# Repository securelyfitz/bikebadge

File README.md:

# 503 party bike badge - 2015
http://503.party/
hardware and software files for attiny-based bicycle badge with rotating flashy reverse-mount LED wheels

## Hardware Description
This project is designed as the badge for donors to the 503 party fund in 2015. The circuit is inteded to use the minimum number of components to get a rotating wheel effect with the LEDs while having a completely clean PCB top side.

## Hardware Theory
Since the number of GPIOs are limited in a tiny chip, some fancy schematic-ing was done.
The bike handlebars (brakes slow down) and pedals (go faster) are two metal areas used as capacitive sensors. This takes up 3 pins - 1 to drive all of them, plus 1 for each sensor.
That leaves 2 pins to control 16 LEDs (14 in final revision for aesthetic reasons) that have to flash in a specific progression:
* the two wheels are identical, so really we need to drive 8 LED positions
* the wheels have two 'pulses' going around them, 180 degrees out of phase, so opposite LEDs are always identical. 4 LED positions
* If LEDs are identical 180 degrees out of phase, then they're opposite 90 degrees out of phase. That means half the LEDs are inversions of the other half. 2 LEDs positons.

If we wire 1 led between VCC and a GPIO, and a second one between a GPIO and GND, then one will be on when GPIO is 1, and the other will be on when GPIO is 0
If we do PWM, then (duty cycle B) = (1 - duty cycle A)
This makes very simple code possible

## Bill of Materials:
* 14x OSRAM reverse-gullwing LEDs (LYT776 YELLOW LED is what i used, 475-2801-1-ND)
* 14x 200 Ohm 1206 SMT Resistor (digikey 311-10MERCT-ND)
* 2x 10M Ohm 0805 Resistor (digikey RMCF0805JT10M0CT-ND)
* 1x ATTiny85 soic8 ()
* 1x 20mm through-hole CR2032 holder and battery

In quantity, BOM cost is about $2-$5 depending on if you can find the reverse-gullwing LEDs

##Building
All of the components are different sizes - if the pads line up it's in the right spot, just make sure pin 1 of the attiny aligns to the dot, and the 'noch' on the LEDS all point clockwise around the wheel.

##Software Description
This code is an Arduino sketch. I used the Sparkfun TinyAVR Programmer and follow the linked hookup guide to get it working: https://www.sparkfun.com/products/11801

The code for sensing the capacitive buttons is based on Paul Stoffregen's updated CapacitiveSensor libarry: https://github.com/PaulStoffregen/CapacitiveSensor
The LEDs are lit with PWM inside a loop. i is rotation point in radians of the wheel
```
for (float i=0;i<(3.1415*2);i+=(3.1415/revs)){
    analogWrite(pwm0,127*(cos(i)+1));
    analogWrite(pwm1,127*(sin(i)+1));
}
```

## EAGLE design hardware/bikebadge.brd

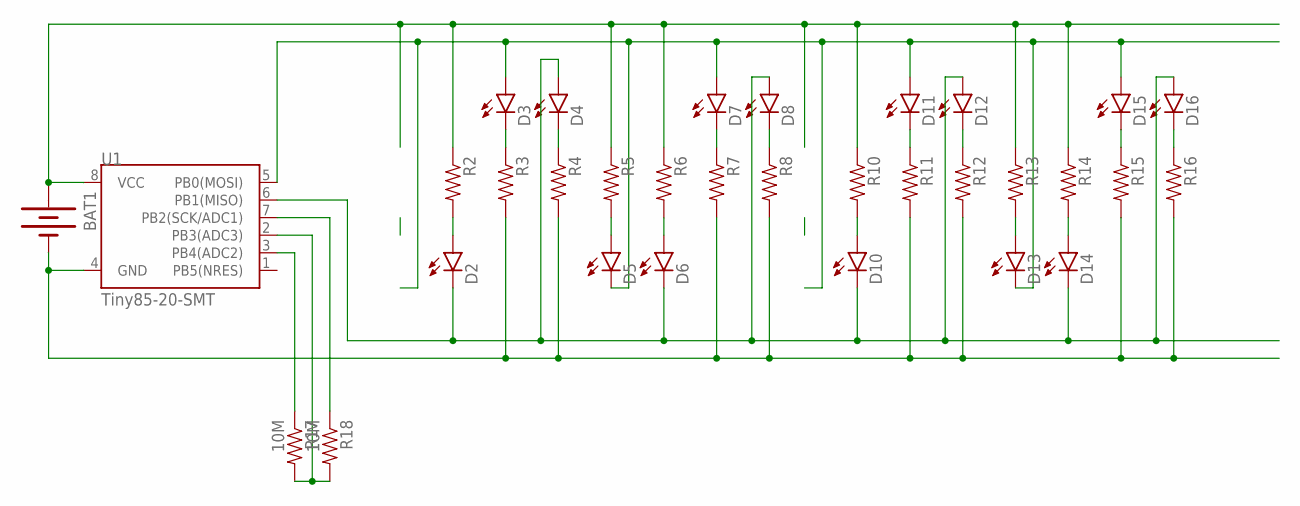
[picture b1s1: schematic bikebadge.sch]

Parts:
BAT1: BATTERY20PTH; BATTCOM_20MM_PTH
D2, D3, D4, D5, D6, D7, D8, D10, D11, D12, D13, D14, D15, D16: LED; LED-REV-MNT
R2, R3, R4, R5, R6, R7, R8, R10, R11, R12, R13, R14, R15, R16: RESISTOR1206; 1206
R17, R18: 10M; 0805
U1: Tiny85-20-SMT; SO08-EIAJ

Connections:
CAP0: R17.1, U1.3 (PB4(ADC2))
CAP1: R18.1, U1.7 (PB2(SCK/ADC1))
GND: BAT1.2 (-), R3.2, R4.2, R7.2, R8.2, R11.2, R12.2, R15.2, R16.2, U1.4 (GND)
unnamed: D2.A, R2.2
unnamed: D3.C, R3.1
unnamed: D4.C, R4.1
unnamed: D5.A, R5.2
unnamed: D6.A, R6.2
unnamed: D16.C, R16.1
unnamed: D15.C, R15.1
unnamed: D10.A, R10.2
unnamed: D12.C, R12.1
unnamed: D11.C, R11.1
unnamed: D8.C, R8.1
unnamed: D7.C, R7.1
unnamed: D13.A, R13.2
unnamed: D14.A, R14.2
PWM0: D3.A, D5.C, D7.A, D11.A, D13.C, D15.A, U1.5 (PB0(MOSI))
PWM1: D2.C, D4.A, D6.C, D8.A, D10.C, D12.A, D14.C, D16.A, U1.6 (PB1(MISO))
SENSE: R17.2, R18.2, U1.2 (PB3(ADC3))
VCC: BAT1.1 (+), R2.1, R5.1, R6.1, R10.1, R13.1, R14.1, U1.8 (VCC)

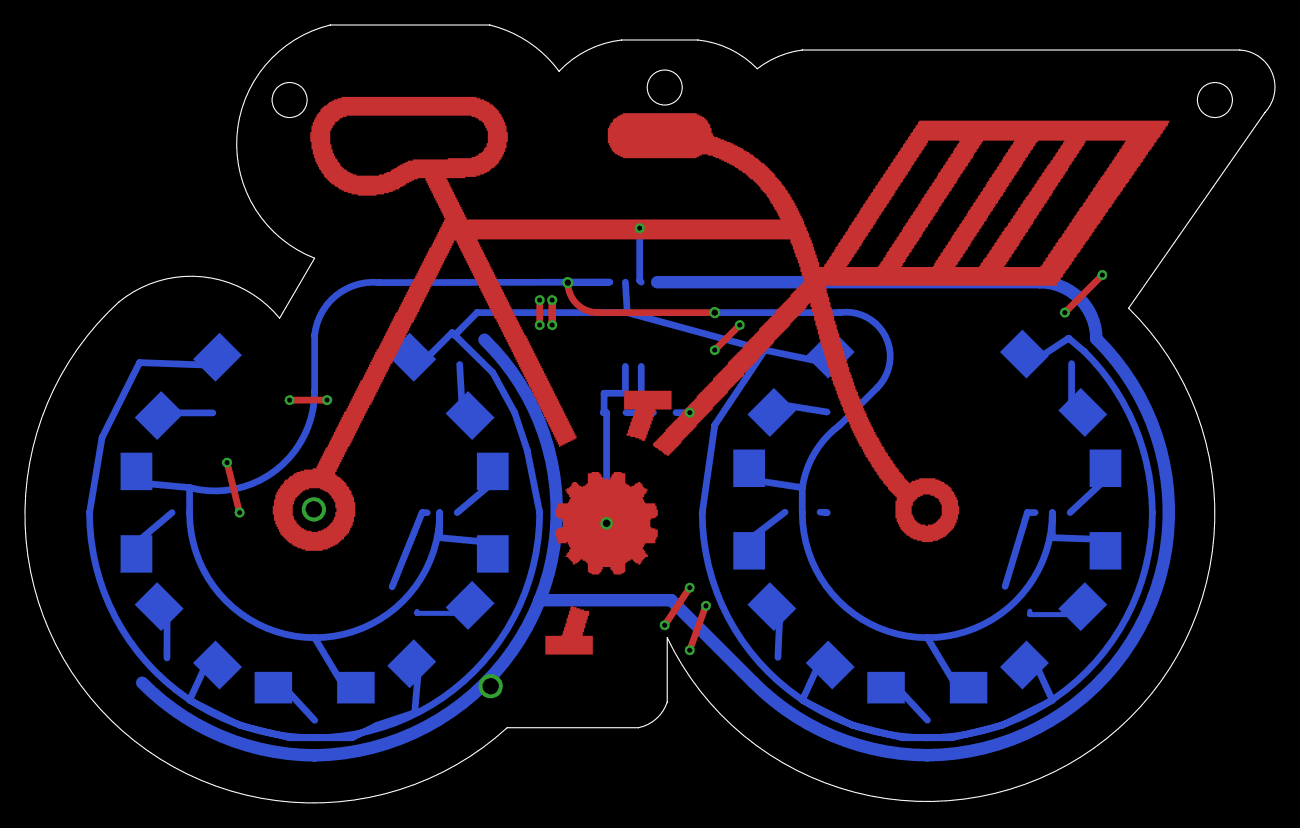
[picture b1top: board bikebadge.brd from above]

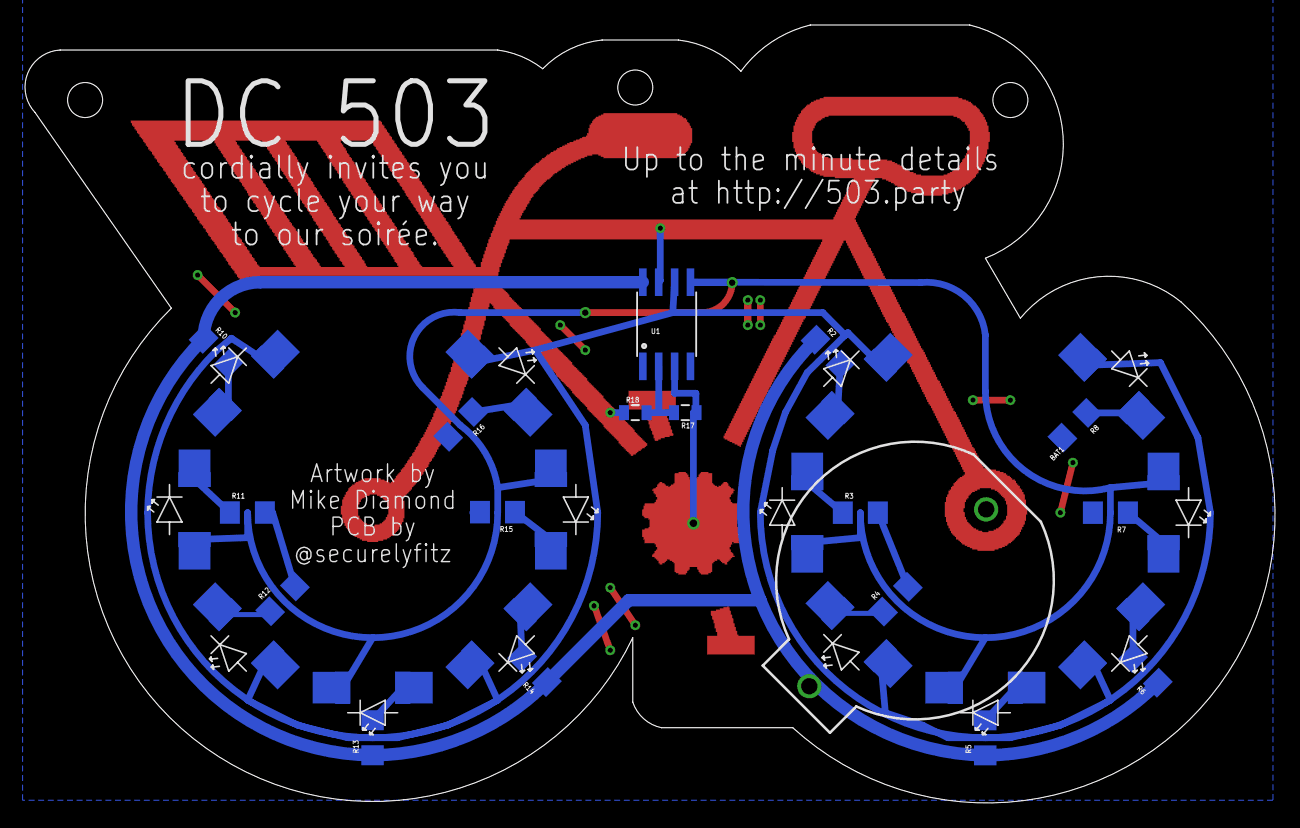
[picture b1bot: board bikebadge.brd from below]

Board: 2 copper layers, 100.0 x 62.2 mm, 33 parts (32 on the bottom side), 21 nets.

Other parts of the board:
U$1: BIKE

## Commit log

2016-09-14 details about parts and building
2016-09-14 fixing 10M resistor size and part number to 0805

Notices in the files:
parts and their libraries:
SparkFun-Passives: Licensing: Creative Commons ShareAlike 4.0 International - https://creativecommons.org/licenses/by-sa/4.0
